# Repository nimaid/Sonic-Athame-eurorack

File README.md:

# *Sonic Athame™* Modular Designs
My open-source Eurorack module designs and prototyping tools.

<div align="center"></div>

## !!! Under Construction !!!
**Stay tuned as I create designs and prepare to begin selling!**

##
### **We give you the tools to direct musical energy via witchcraft!**
At Sonic Athame Modular, we see the untapped potential of the Eurorack format as a *truly* modular platform. While there are thousands of modules out there already, many of them hide away the magic of their inner workings from the musician. You put a signal in, something mysterious involving electronics happens, and a different signal comes out. Even if the musician did find the schematic for the module, they are still unable to re-configure how the internals are wired together without modifying the circuit board.

While these "integrated" modules remove complexity from patches and save space, they also inherently limit the creativity and understanding of the musician. Sonic Athame takes a different approach. We make modules that are 100% reconfigurable, similar to a semi-modular synth. Instead of one integrated module, we design sets of cleverly interconnected general-purpose "submodules". By default, these submodules are connected together to do the same thing as their integrated counterparts, but with the added benefit of being able to change how they are wired together on-the-fly to create new functionality.

Take, for example, an envelope follower. You will find most of the modules on the market have the following inputs and outputs:
* In
* Out
* Envelope Out
* Gate Out

There is nothing wrong with this way of doing things, as it makes for a small module that does it's job. However, consider an envelope follower module with the following inputs and outputs:
* In
* Out
* Full-Wave Rectifier [FWR] In (connected to `Out` when unplugged)
* FWR Out
* Low-pass Filter In (connected to `FWR Out` when unplugged)
* Low-pass Filter Out (also the `Envelope Out` if not bypassed with patch cables)
* CV Knob Out
* Comparator + In (connected to `Low-pass Filter In` when unplugged)
* Comparator - In (connected to `CV Knob Out` when unplugged)
* Comparator Out (also the `Gate Out` if not bypassed with patch cables)

When only `In`, `Out`, `Low-pass Filter Out`, and `Comparator Out` are connected, the module works like a normal envelope follower. However, if you do not need an envelope follower in your current patch, you can also use it as a utility module with:
* 1x Manual (Knob) Amplifier
* 1x Full-Wave Rectifier
* 1x Manual (Knob) Low-pass filter
* 1x CV Knob
* 1x Comparator

While this second module will take up more space in the rack than the first one due to having more input and output jacks, it is almost never going to be "dead weight". One or two of the submodules are always going to be useful, no matter what. It's even possible to combine submodules to create entirely new functionality. In essence, Sonic Athame designs modules that provide an "electronics toolkit" tailored for the job at hand, while allowing each individual "tool" to be re-used in new and creative ways.

We also design "Elemental" modules. These are essentially individual submodules from our other modules, but with all though-hole parts and a focus on cost effectiveness. These are sold as soldering kits with all the required parts, which are easy to assemble even for beginners. This allows a musician to pick and choose which utilities they want while spending the bare minimum.

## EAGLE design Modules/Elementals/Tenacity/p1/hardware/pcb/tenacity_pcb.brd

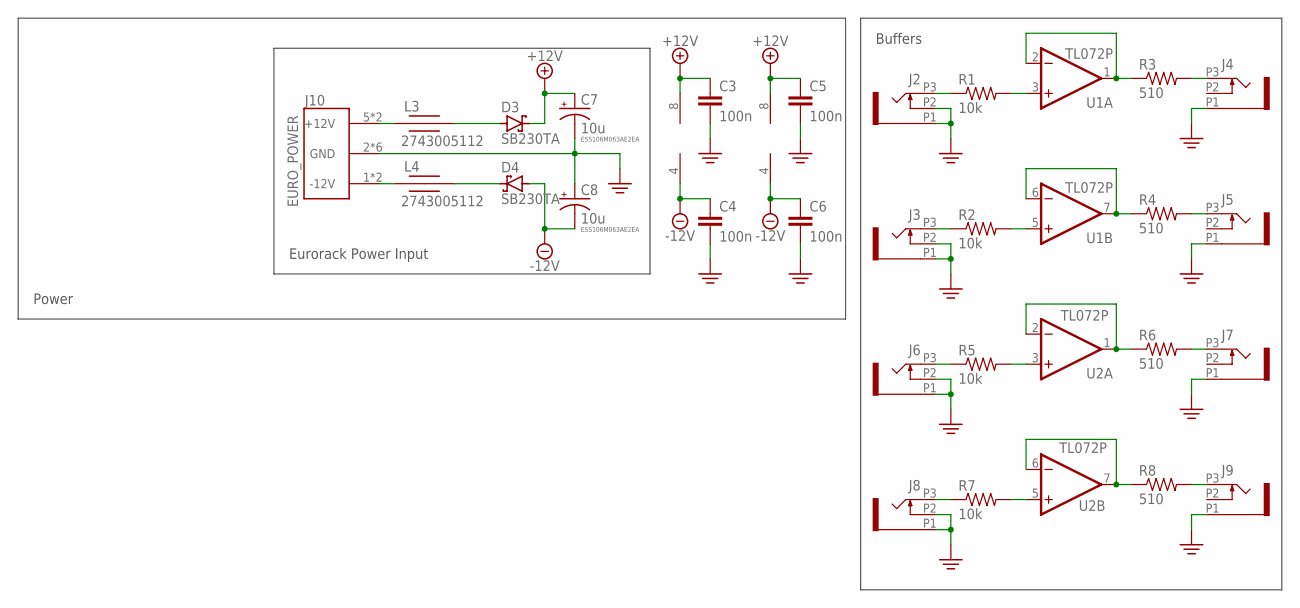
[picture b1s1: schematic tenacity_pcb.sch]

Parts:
C3, C4, C5, C6: 100n; C025-024X044
C7, C8: 10u; TT2D5
D3, D4: SB230TA; 0207/2V-POL
J2, J3, J4, J5, J6, J7, J8, J9: WQP-PJ398SM6; WQP_PJ_301M6
J10: EURO_POWER
L3, L4: 2743005112; 0207/2V
R1, R2, R5, R7: 10k; 0207/2V
R3, R4, R6, R8: 510; 0207/2V
U1, U2: TL072P; DIL08

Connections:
+12V: C3.1, C5.1, C7.+, D3.C, U1.8 (V+), U2.8 (V+)
-12V: C4.1, C6.1, C8.-, D4.A, U1.4 (V-), U2.4 (V-)
GND: C3.2, C4.2, C5.2, C6.2, C7.-, C8.+, J2.P1 (1), J2.P2 (2), J3.P1 (1), J3.P2 (2), J4.P1 (1), J5.P1 (1), J6.P1 (1), J6.P2 (2), J7.P1 (1), J8.P1 (1), J8.P2 (2), J9.P1 (1), J10.2 (GND), J10.3 (GND), J10.4 (GND), J10.7 (GND), J10.8 (GND), J10.9 (GND)
unnamed: J8.P3 (3), R7.1
unnamed: R7.2, U2.5 (+IN)
unnamed: R1.2, U1.3 (+IN)
unnamed: J2.P3 (3), R1.1
unnamed: J5.P3 (3), R4.2
unnamed: J4.P3 (3), R3.2
unnamed: R2.2, U1.5 (+IN)
unnamed: J9.P3 (3), R8.2
unnamed: J7.P3 (3), R6.2
unnamed: R4.1, U1.6 (-IN), U1.7 (OUT)
unnamed: J3.P3 (3), R2.1
unnamed: R3.1, U1.1 (OUT), U1.2 (-IN)
unnamed: R8.1, U2.6 (-IN), U2.7 (OUT)
unnamed: J6.P3 (3), R5.1
unnamed: R5.2, U2.3 (+IN)
unnamed: R6.1, U2.1 (OUT), U2.2 (-IN)
unnamed: D3.A, L3.2
unnamed: D4.C, L4.2
unnamed: J10.1 (-12V), J10.10 (-12V), L4.1
unnamed: J10.5 (+12V), J10.6 (+12V), L3.1

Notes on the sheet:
Power
Buffers
ESS106M063AE2EA
Eurorack Power Input

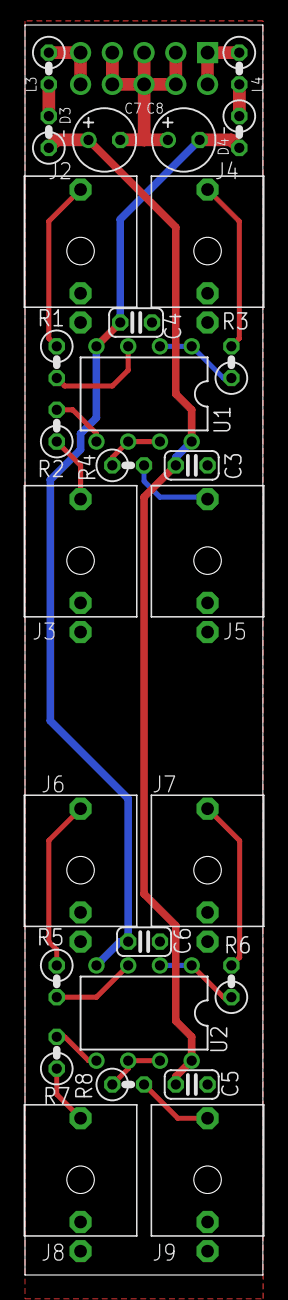
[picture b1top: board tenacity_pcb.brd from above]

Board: 2 copper layers, 19.0 x 100.0 mm, 31 parts (1 on the bottom side), 23 nets.

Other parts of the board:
U$1: PANEL_REF_4U
U$2: LOGO-65MIL-BSILK

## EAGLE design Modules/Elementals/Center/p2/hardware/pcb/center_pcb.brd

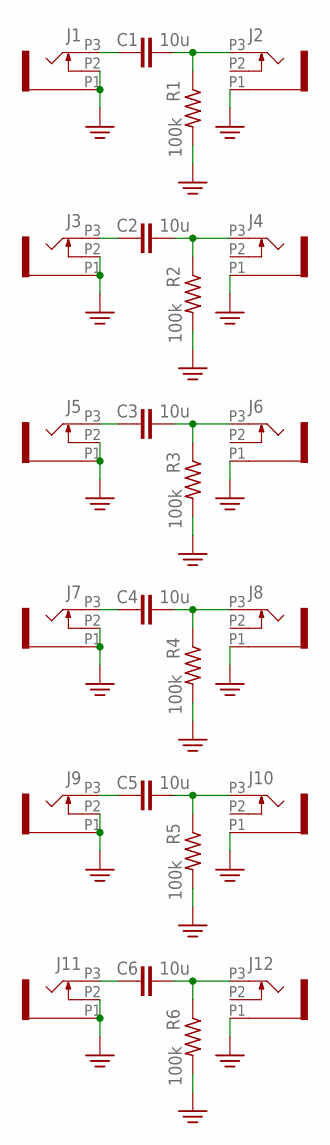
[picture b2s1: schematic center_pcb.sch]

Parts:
C1, C2, C3, C4, C5, C6: 10u; C025-024X044
J1, J2, J3, J4, J5, J6, J7, J8, J9, J10, J11, J12: WQP-PJ398SM6; WQP_PJ_301M6
R1, R2, R3, R4, R5, R6: 100k; 0207/2V

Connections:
GND: J1.P1 (1), J1.P2 (2), J2.P1 (1), J3.P1 (1), J3.P2 (2), J4.P1 (1), J5.P1 (1), J5.P2 (2), J6.P1 (1), J7.P1 (1), J7.P2 (2), J8.P1 (1), J9.P1 (1), J9.P2 (2), J10.P1 (1), J11.P1 (1), J11.P2 (2), J12.P1 (1), R1.2, R2.2, R3.2, R4.2, R5.2, R6.2
unnamed: C1.1, J1.P3 (3)
unnamed: C1.2, J2.P3 (3), R1.1
unnamed: C2.2, J4.P3 (3), R2.1
unnamed: C2.1, J3.P3 (3)
unnamed: C3.2, J6.P3 (3), R3.1
unnamed: C3.1, J5.P3 (3)
unnamed: C4.1, J7.P3 (3)
unnamed: C4.2, J8.P3 (3), R4.1
unnamed: C5.1, J9.P3 (3)
unnamed: C5.2, J10.P3 (3), R5.1
unnamed: C6.2, J12.P3 (3), R6.1
unnamed: C6.1, J11.P3 (3)

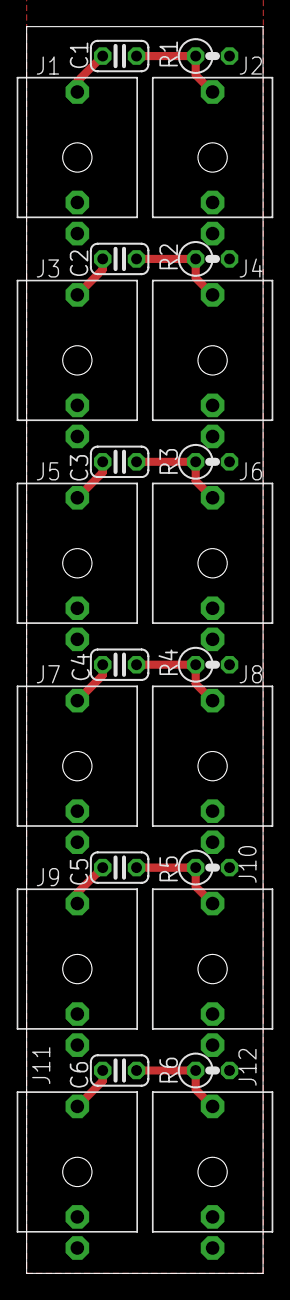
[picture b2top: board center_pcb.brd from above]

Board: 2 copper layers, 17.8 x 93.7 mm, 26 parts (1 on the bottom side), 13 nets.

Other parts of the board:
U$2: PANEL_REF_4U
U$3: LOGO-65MIL-TSILK

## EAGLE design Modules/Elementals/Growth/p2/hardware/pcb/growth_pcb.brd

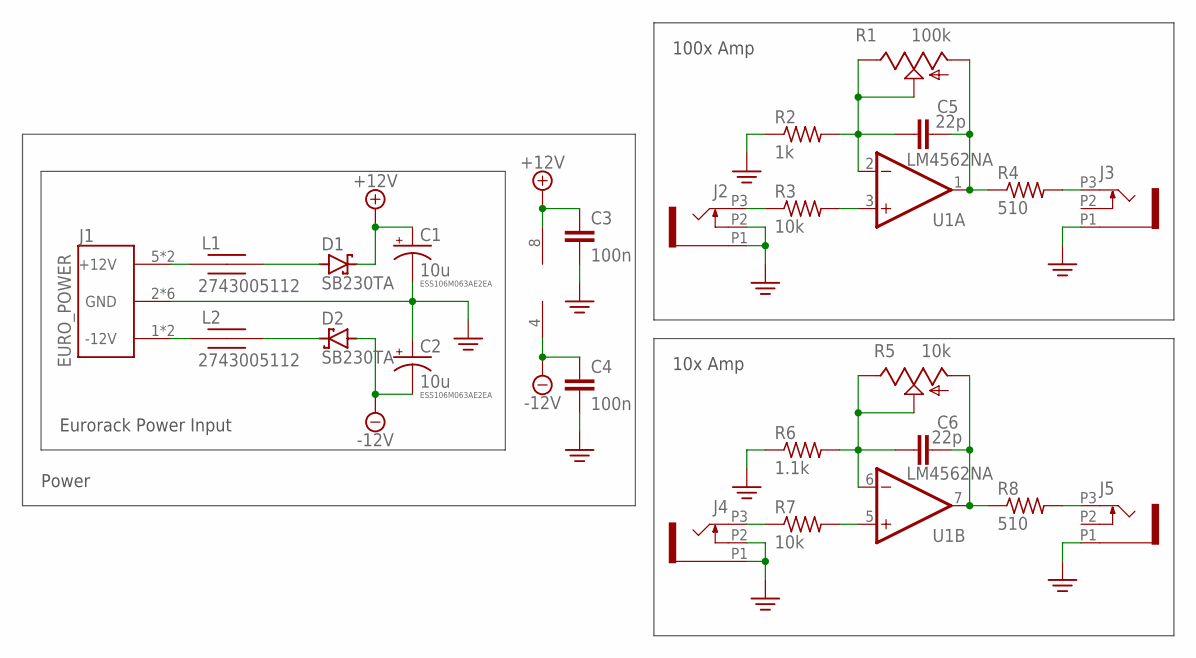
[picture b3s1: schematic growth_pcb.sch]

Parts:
C1, C2: 10u; TT2D5
C3, C4: 100n; C025-024X044
C5, C6: 22p; C025-024X044
D1, D2: SB230TA; 0207/2V-POL
J1: EURO_POWER
J2, J3, J4, J5: WQP-PJ398SM6; WQP_PJ_301M6
L1, L2: 2743005112; 0207/2V
R1: 100k; ALPHA_POT_VERTICAL
R2: 1k; 0207/2V
R3, R7: 10k; 0207/2V
R4, R8: 510; 0207/2V
R5: 10k; ALPHA_POT_VERTICAL
R6: 1.1k; 0207/2V
U1: LM4562NA; DIL08

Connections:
+12V: C1.+, C3.1, D1.C, U1.8 (V+)
-12V: C2.-, C4.1, D2.A, U1.4 (V-)
GND: C1.-, C2.+, C3.2, C4.2, J1.2 (GND), J1.3 (GND), J1.4 (GND), J1.7 (GND), J1.8 (GND), J1.9 (GND), J2.P1 (1), J2.P2 (2), J3.P1 (1), J4.P1 (1), J4.P2 (2), J5.P1 (1), R2.1, R6.1
unnamed: C5.1, R1.P$1 (E), R1.P$2 (S), R2.2, U1.2 (-IN)
unnamed: C5.2, R1.P$3 (A), R4.1, U1.1 (OUT)
unnamed: R3.2, U1.3 (+IN)
unnamed: J2.P3 (3), R3.1
unnamed: J5.P3 (3), R8.2
unnamed: J3.P3 (3), R4.2
unnamed: R7.2, U1.5 (+IN)
unnamed: C6.1, R5.P$1 (E), R5.P$2 (S), R6.2, U1.6 (-IN)
unnamed: C6.2, R5.P$3 (A), R8.1, U1.7 (OUT)
unnamed: J4.P3 (3), R7.1
unnamed: D1.A, L1.2
unnamed: D2.C, L2.2
unnamed: J1.1 (-12V), J1.10 (-12V), L2.1
unnamed: J1.5 (+12V), J1.6 (+12V), L1.1

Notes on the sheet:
Power
100x Amp
10x Amp
ESS106M063AE2EA
Eurorack Power Input

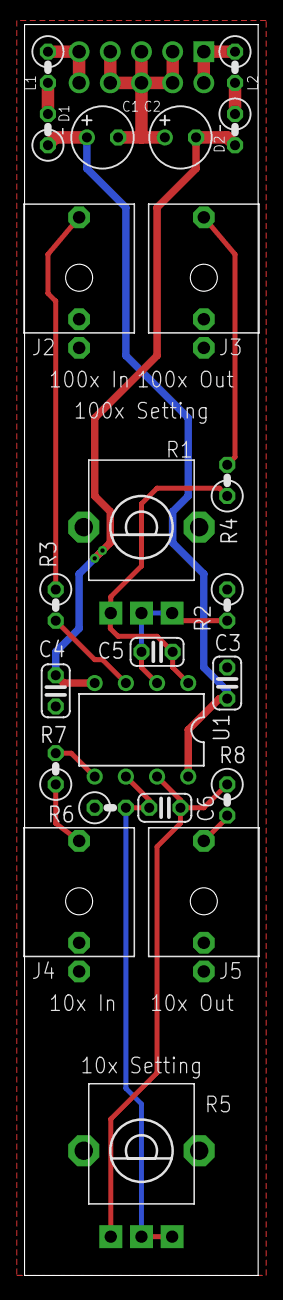
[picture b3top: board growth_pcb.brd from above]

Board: 2 copper layers, 19.0 x 101.9 mm, 26 parts (1 on the bottom side), 17 nets.

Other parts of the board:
U$1: PANEL_REF_4U
U$2: LOGO-65MIL-BSILK

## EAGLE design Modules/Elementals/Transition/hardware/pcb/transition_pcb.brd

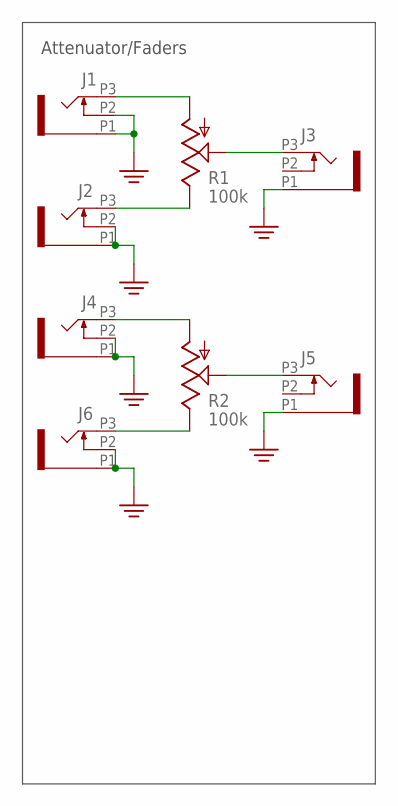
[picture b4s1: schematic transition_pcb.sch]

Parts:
J1, J2, J3, J4, J5, J6: WQP-PJ398SM6; WQP_PJ_301M6
R1, R2: 100k; ALPHA_POT_VERTICAL

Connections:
GND: J1.P1 (1), J1.P2 (2), J2.P1 (1), J2.P2 (2), J3.P1 (1), J4.P1 (1), J4.P2 (2), J5.P1 (1), J6.P1 (1), J6.P2 (2)
unnamed: J2.P3 (3), R1.P$1 (E)
unnamed: J3.P3 (3), R1.P$2 (S)
unnamed: J1.P3 (3), R1.P$3 (A)
unnamed: J4.P3 (3), R2.P$3 (A)
unnamed: J6.P3 (3), R2.P$1 (E)
unnamed: J5.P3 (3), R2.P$2 (S)

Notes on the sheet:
Attenuator/Faders

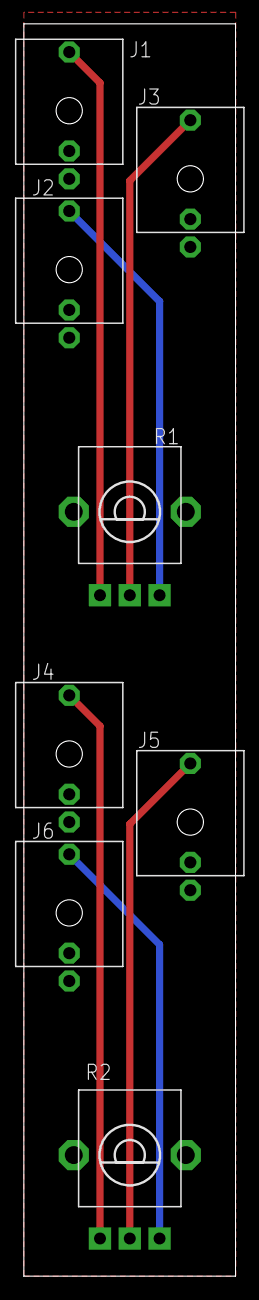
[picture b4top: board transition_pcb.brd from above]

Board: 2 copper layers, 17.8 x 105.1 mm, 10 parts (0 on the bottom side), 7 nets.

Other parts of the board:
U$1: PANEL_REF_4U
U$2: LOGO-65MIL-BSILK

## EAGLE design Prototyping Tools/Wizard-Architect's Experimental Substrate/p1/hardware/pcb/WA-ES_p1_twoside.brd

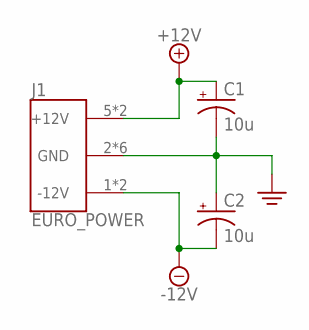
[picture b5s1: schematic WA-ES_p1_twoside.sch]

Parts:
C1, C2: 10u; TT2D5
J1: EURO_POWER

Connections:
+12V: C1.+, J1.5 (+12V), J1.6 (+12V)
-12V: C2.-, J1.1 (-12V), J1.10 (-12V)
GND: C1.-, C2.+, J1.2 (GND), J1.3 (GND), J1.4 (GND), J1.7 (GND), J1.8 (GND), J1.9 (GND)

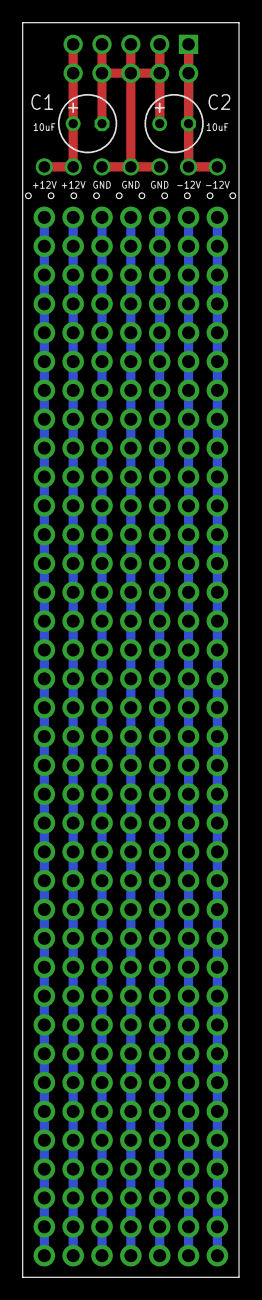
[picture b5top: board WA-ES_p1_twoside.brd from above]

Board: 2 copper layers, 19.1 x 110.5 mm, 3 parts (1 on the bottom side), 3 nets.

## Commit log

2019-08-03 Started PSU PCB
2019-08-03 Added AC input
2019-08-04 Add fuse holder
2020-06-16 Started envelope follower
2020-06-16 Basic circuit/layout captured
2020-06-16 more changes
2020-06-17 ch-ch-ch-c
2020-06-18 I'm using Mutable Instruments' Ears module as a starting point for Followers
2020-06-18 Clean up power section
2020-06-18 Fixed op-amps
2020-06-18 Slew rate limiter
2020-06-18 bomf
2020-06-18 Input resistor
2020-06-18 Filter
2020-06-18 Restructure, fixed LEDs
2020-06-18 More labels, voltage reference
2020-06-18 Comparator
2020-06-18 Made schematic
2020-06-18 Added slow slew cap (no sw yet)
2020-06-19 CV Pot
2020-06-19 Restructured to be like senpai Mutable owo
2020-06-19 Added stability resistor
2020-06-21 Forgot a wire
2020-07-24 Rename
2020-07-24 Found Alpha pot replacements
2020-07-30 Prices n stuff
    can't get enough
2020-07-30 PCL structure change
2020-08-01 move
2020-08-01 No fcl
2020-08-09 Rename PSU
2020-08-09 Added screw terms
2020-08-09 Started work on breadboard reference design block
2020-08-09 Removed schematic from breadboard ref
2020-08-09 Started WAM-D
2020-08-09 WAM-D progress
2020-08-09 Finalize v1
2021-01-16 Added more datasheets
2021-01-19 Started work on Elemental Growth, a 100x and 10x amplifier.
2021-01-19 Finalized(?)
2021-01-19 Better power layout
2021-01-19 Add version
2021-01-19 Begin work on Elemental Center
2021-01-20 Finished center pcb and panel
2021-01-20 V2 of Elemental Growth started. 10x opamp was backwards (doy), and feedback caps were not present.
2021-01-20 Elemental growth panel v1
2021-01-20 Started v2 of elemental center, grounded inputs by default.
2021-01-20 Changed bypass caps to 22p for better HF response. https://northcoastsynthesis.com/news/understanding-stabilization-capacitors/
2021-01-20 Ignore EAGLE raw MFG outputs
2021-01-20 Minor wiring fix
2021-01-23 Made custom eurorack prototyping stripboard
2021-01-23 Updated Elemental Center with more compact parts
2021-01-23 Used more compact components for Elemental Growth
2021-01-23 Update PCL
2021-01-23 whoops
2021-01-23 Remove garbage
2021-01-23 Refactored versioning for Elemental Center
2021-01-23 Refactored versioning for Elemental Growth
2021-01-23 Refactored versioning for strip board
2021-01-23 Refactored versioning for bb power breakout
2021-01-23 Finally created the logo! <3
2021-01-23 More logo configurations
2021-01-23 Massive readme update
2021-01-23 Updated Logo (hilt)
2021-01-24 EAGLE compatable version of the logo, using https://gfwilliams.github.io/svgtoeagle/
2021-01-24 4u eagle logo
2021-01-25 Removed pre-emptive zips
2021-01-25 Rename eagle files
2021-01-25 Replaced board holes/outlines with standard library component
2021-01-25 Added logo to growth panel
2021-01-25 Reposition
2021-01-26 Started Elemental Tenacity PCB
2021-01-26 Started Elemental Transition
2021-01-26 Added panel ref, resized
2021-01-26 Fixed Fusion 360 links
2021-01-26 30 mil logo
2021-01-26 Remove two sided stripboard
2021-01-26 Remove xip
2021-01-26 Rename proto tools
2021-01-26 Start p2 of stripboard
2021-01-26 Moved WAMD
2021-01-26 Remove mana source ideas
2021-01-26 Add logo
2021-01-27 Extreme improvements on stripboard v2
2021-01-28 Elemental Center PCB ready
2021-01-28 Stripboard v2 ready to order
2021-01-28 Finalized center v2
2021-01-28 Cleaner schematic layout
2021-01-28 Moved design blocks
2021-01-28 Added eurorack power design block
2021-01-28 Updated stripboard with design block
2021-01-28 New standard power input block on Growth V2
2021-01-28 Stripboard p2 gerbers added
2021-01-28 Finished elemental growth p2 PCB
2021-01-28 Growth p2 gerbers
2021-01-28 Add center gerbers
2021-01-28 Finished Transition p2
2021-01-28 eagle vers.
2021-01-28 Moved transition to subfolder
2021-01-28 Add transition gerber
2021-01-28 Finalized tenacity p1
2021-01-28 tenacity p1 gerbers
2021-01-28 fixed name
2021-01-28 Started center p2 panel
2021-01-28 Removed accidental panels
2021-01-29 center p2 panel done
2021-01-29 center panel gerbers
2021-01-29 Started growth p2 panel
2021-01-31 p1 of CLB cases
2023-06-03 Simplified drum machine code
2023-06-03 Added polytrigger mode
2023-06-03 Added default drum samples
2023-06-03 Moved
2023-06-03 Broke out drum samples into a header
2023-06-04 Added shift register
